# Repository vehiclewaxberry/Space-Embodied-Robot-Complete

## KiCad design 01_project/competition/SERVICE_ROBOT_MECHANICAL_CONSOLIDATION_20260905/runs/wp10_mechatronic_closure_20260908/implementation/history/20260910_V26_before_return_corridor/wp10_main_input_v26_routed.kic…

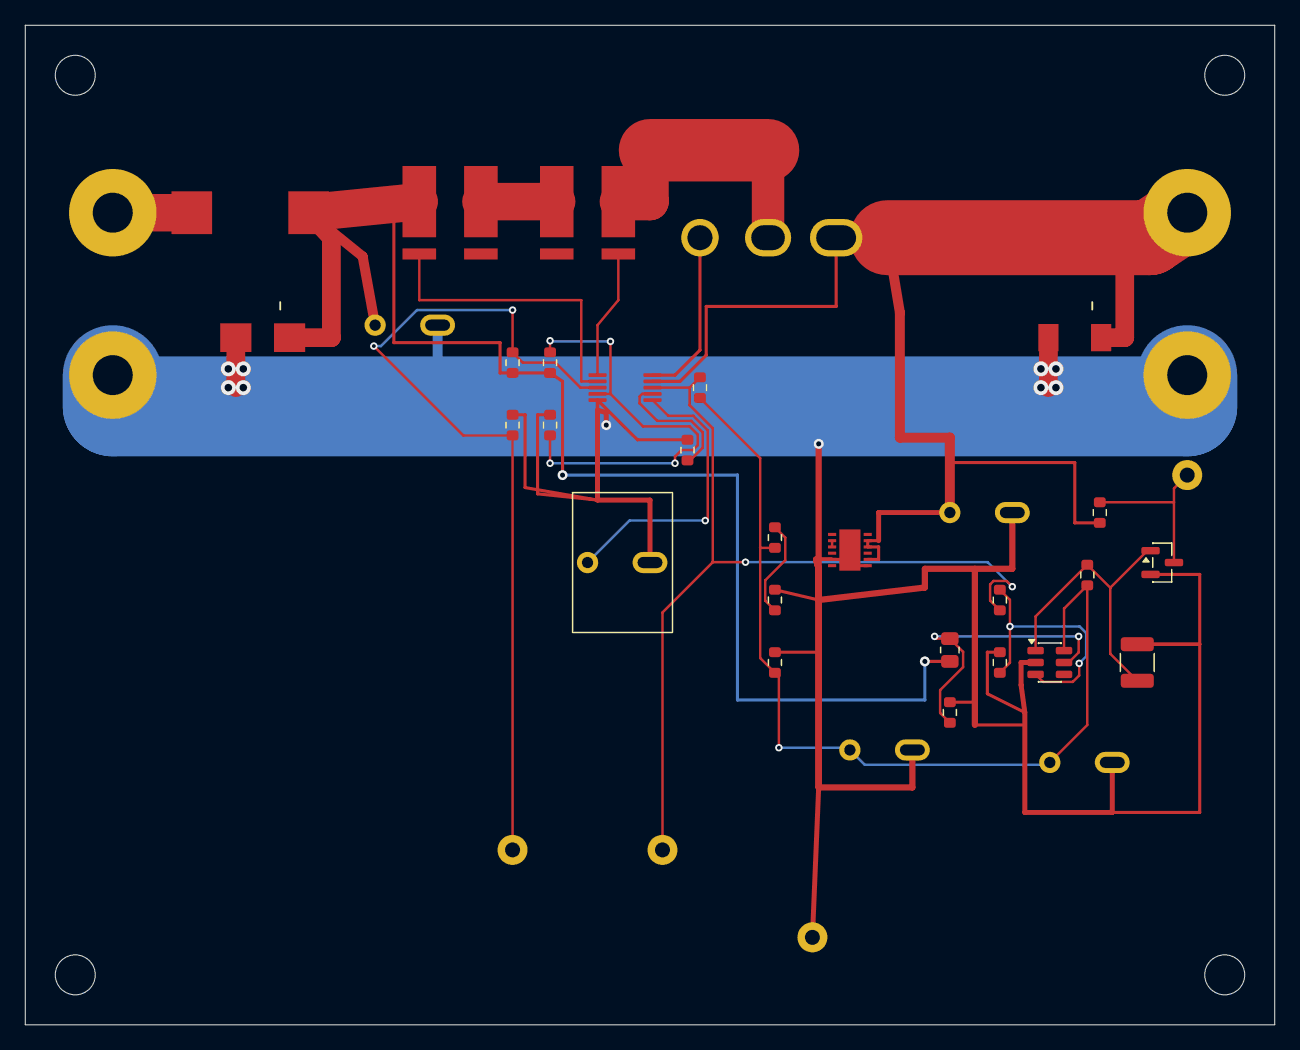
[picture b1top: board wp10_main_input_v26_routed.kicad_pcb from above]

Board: 2 copper layers, 100.0 x 80.0 mm, 43 parts (0 on the bottom side), 18 nets.

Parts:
C201: MKP2C041001N00JSSD; C201_MKP2_1uF_P5_Slot2
C202, C213: MKP2D031001F00JSSD; MKP2_D031001F00_P5_Slot2
C211: MKS2D041501M00JSSD; MKS2_D041501M00_P5_Slot2
C212: MKS2D044701O00JSSD; MKS2_D044701O00_P5_Slot2
D201: SMBJ30A-13-F; SMBJ30A_A1K2
D202: STPS3H100U; STPS3H100U_A1K2
F201: 1025HC30-RTR; Fuse_Eaton_1025HC_20to30A_3p25x3p43_P9p35
MH1, MH2, MH3, MH4: (no value)
PORT_BAT_PLUS: PROJECT_WIRE_LANDING_NOT_OEM_CONNECTOR
PORT_BAT_RETURN: PROJECT_WIRE_LANDING_NOT_OEM_CONNECTOR
PORT_CHB_PLUS: PROJECT_WIRE_LANDING_NOT_OEM_CONNECTOR
PORT_CHB_RETURN: PROJECT_WIRE_LANDING_NOT_OEM_CONNECTOR
PORT_ENABLE: PROJECT_WIRE_LANDING_NOT_OEM_CONNECTOR
PORT_PGD: PROJECT_WIRE_LANDING_NOT_OEM_CONNECTOR
PORT_RESET: PROJECT_WIRE_LANDING_NOT_OEM_CONNECTOR
PORT_SIGNAL_RETURN: PROJECT_WIRE_LANDING_NOT_OEM_CONNECTOR
Q201: IXTH75N10L2; IXTH_TO247_G1D2S3_P5p45_Slots
Q204: 2N7002K-7; SOT-23
R201: WSLP27262L000FEA; WSLP2726_KelvinSplit_TwoTerminals
R202: WSLP2726L2000FEA; WSLP2726_KelvinSplit_TwoTerminals
R203: TNPW060347K5BEEA; R_0603_1608Metric
R204: TNPW06035K90BEEA; R_0603_1608Metric
R205: TNPW0603120KBEEA; R_0603_1608Metric
R206, R212, R216: TNPW060310K0BEEA; R_0603_1608Metric
R207: TNPW060330K1BEEA; R_0603_1608Metric
R211: TNPW060338K3BEEA; R_0603_1608Metric
R213: TNPW06034K70FEEA; R_0603_1608Metric
R214: TNPW06033K48BEEA; R_0603_1608Metric
R215: TNPW0805374KBEEA; R_0805_2012Metric
R217: TNPW060333K0FEEA; R_0603_1608Metric
R218: TNPW12102M20FEEA; R_1210_3225Metric
R219: TNPW0603100KFEEA; R_0603_1608Metric
R220: TNPW060310K0FEEA; R_0603_1608Metric
R221: TNPW0603100RFEEA; R_0603_1608Metric
U201: LM5069MM-1; LM5069_DGS10_P0p5_NoEP
U205: LT3013EDE#PBF; LT3013_DE12_EP13_3x4_Pin1LeftTop
U206: TPS3808G01DBVR; SOT-23-6

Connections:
WP10_BAT_PROTECTED_PLUS: F201.1, PORT_BAT_PLUS.1
WP10_CHB_ENABLE: PORT_ENABLE.1, Q204.3, R219.2
WP10_CHB_ENABLE_GATE: Q204.1, R217.2, R218.1, U206.1
WP10_HS_OVLO: R205.2, R206.1, U201.4
WP10_HS_PGD: PORT_PGD.1, R214.2, R221.1, U201.8
WP10_HS_POWER_LIMIT: R207.1, U201.7
WP10_HS_TIMER: C201.1, U201.6
WP10_HS_UVLO: PORT_RESET.1, R203.2, R204.1, U201.3
WP10_INPUT_RETURN: C201.2, C202.2, C211.2, C212.2, C213.2, D201.1, D202.1, PORT_BAT_RETURN.1, PORT_CHB_RETURN.1, PORT_SIGNAL_RETURN.1, Q204.2, R204.2, R206.2, R207.2, R212.2, R213.2, R216.2, R218.2, R220.2, U201.5, U205.5, U205.7, U205.13, U206.2
WP10_MAIN_FUSED: C202.1, D201.2, F201.2, R201.1, R203.1, R205.1, R215.1, U201.2
WP10_MAIN_GATE: Q201.1, U201.10
WP10_MAIN_SENSE: Q201.2, R202.2, U201.1
WP10_PRECHARGED_PLUS: C211.1, D202.2, PORT_CHB_PLUS.1, Q201.3, R219.1, U201.9, U205.8, U205.10, U205.11
WP10_SENSE_MID: R201.2, R202.1
WP10_STARTUP_ADJ: R211.2, R212.1, U205.4
WP10_STARTUP_BIAS: C212.1, C213.1, R211.1, R213.1, R214.1, R217.1, U205.2, U205.3, U206.6
WP10_STARTUP_INPUT_SENSE: R215.2, R216.1, U206.5
WP10_STARTUP_PG_RECEIVER: R220.1, R221.2, U206.3

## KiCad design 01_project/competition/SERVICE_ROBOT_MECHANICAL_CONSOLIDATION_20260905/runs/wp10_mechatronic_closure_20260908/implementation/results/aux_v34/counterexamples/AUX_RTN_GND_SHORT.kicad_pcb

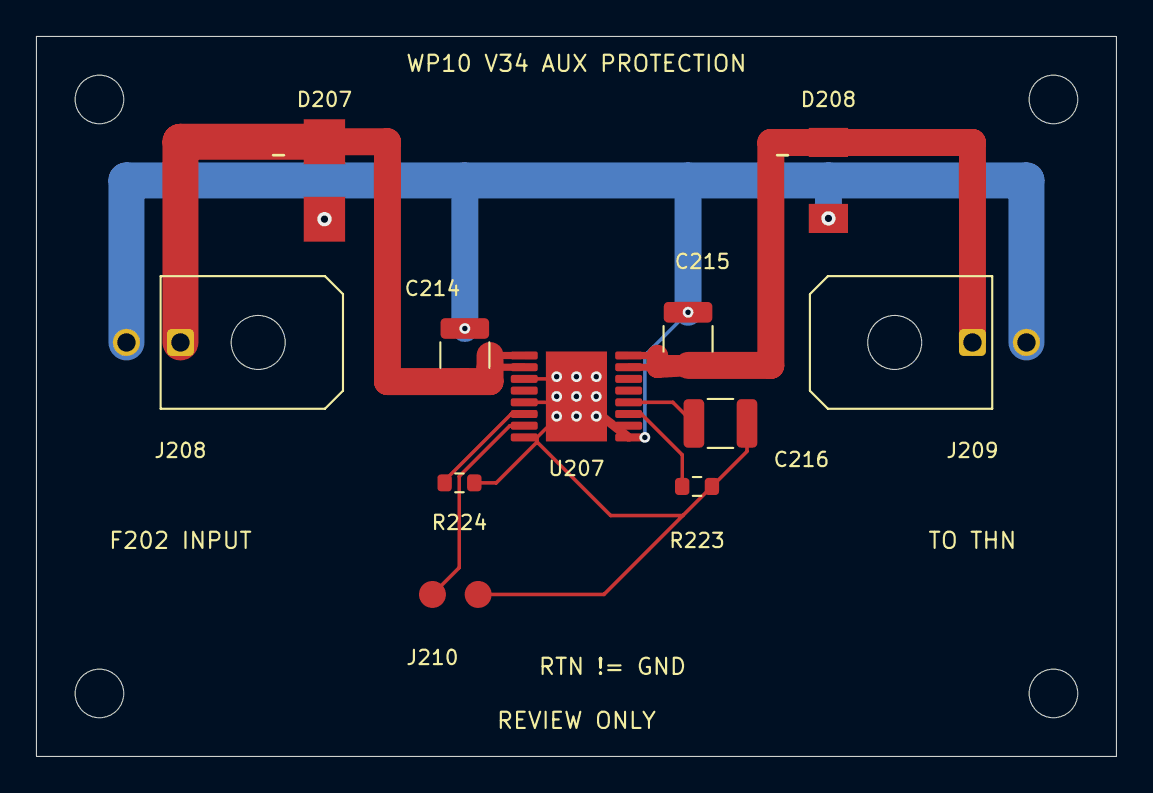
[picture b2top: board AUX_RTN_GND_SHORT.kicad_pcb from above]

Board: 2 copper layers, 60.0 x 40.0 mm, 15 parts (0 on the bottom side), 8 nets.

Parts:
C214, C215, C216: 100nF 100V C0G; C_1210_3225Metric
D207: SMBJ30CA-13-F; SMBJ30A_A1K2
D208: STPS3H100U; STPS3H100U_K1A2
J208: 43045-0200 IN; Molex_Micro-Fit_3.0_43045-0200_2x01_P3.00mm_Horizontal
J209: 43045-0200 TO_THN; Molex_Micro-Fit_3.0_43045-0200_2x01_P3.00mm_Horizontal
J210: LOCAL_RESET_TEST_PADS; ResetTestPads
MH34_1, MH34_2, MH34_3, MH34_4: M2.5 NPTH 2.7mm; MountingHole_2.7mm_M2.5
R223: 5.36k; R_0603_1608Metric
R224: 402k; R_0603_1608Metric
U207: TPS26600PWPR; TPS26600_PWP16_EP17

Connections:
WP10_AUX_DVDT: C216.1, U207.12
WP10_AUX_FUSED: C214.1, D207.2, J208.1, U207.1, U207.2
WP10_AUX_ILIM: R223.1, U207.11
WP10_AUX_LIMITED: C215.1, D208.1, J209.1, U207.15, U207.16
WP10_AUX_MODE: R224.1, U207.6
WP10_AUX_PROTECT_RTN: C216.2, J210.2, R223.2, R224.2, U207.3, U207.5, U207.8, U207.17
WP10_AUX_RESET: J210.1, U207.7
WP10_INPUT_RETURN: C214.2, C215.2, D207.1, D208.2, J208.2, J209.2, U207.9

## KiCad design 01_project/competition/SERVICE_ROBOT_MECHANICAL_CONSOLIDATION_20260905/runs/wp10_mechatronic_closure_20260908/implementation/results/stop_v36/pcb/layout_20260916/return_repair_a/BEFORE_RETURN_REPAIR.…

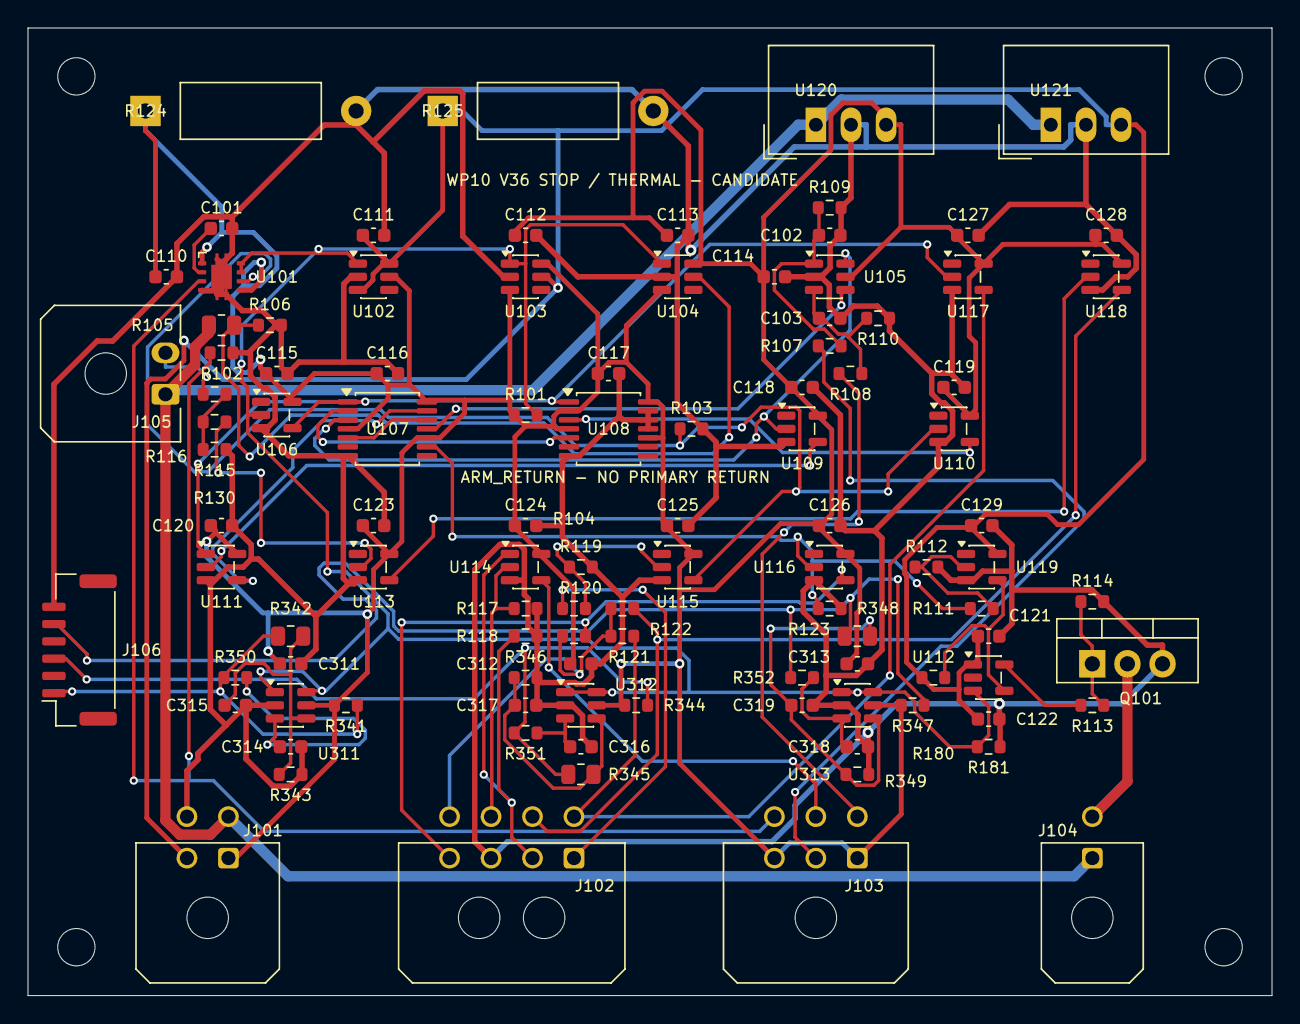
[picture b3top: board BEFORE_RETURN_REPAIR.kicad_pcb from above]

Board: 2 copper layers, 90.0 x 70.0 mm, 107 parts (0 on the bottom side), 49 nets.

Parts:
C101: C0603C121F5GACTU / C0603C121F5GACTU; C_0603_1608Metric
C102, C103, C122: C0603C105K4RACTU / 1uF X7R 16V 10%; C_0603_1608Metric
C110, C111, C112, C113, C114, C115, C116, C117, C118, C119, C120, C121, C123, C124, C125, C126, C127, C128, C129, C311, C312, C313: C0603C104K3RACTU / 100nF X7R 25V 10%; C_0603_1608Metric
C314, C315, C316, C317, C318, C319: 1nF; C_0603_1608Metric
HSTOP1, HSTOP2, HSTOP3, HSTOP4: M2.5; MountingHole_2.7mm_M2.5
J101: 430450400; Molex_Micro-Fit_3.0_43045-0400_2x02_P3.00mm_Horizontal
J102: 430450800; Molex_Micro-Fit_3.0_43045-0800_2x04_P3.00mm_Horizontal
J103: 430450600; Molex_Micro-Fit_3.0_43045-0600_2x03_P3.00mm_Horizontal
J104: 430450200; Molex_Micro-Fit_3.0_43045-0200_2x01_P3.00mm_Horizontal
J105: 436500200; Molex_Micro-Fit_3.0_43650-0200_1x02_P3.00mm_Horizontal
J106: SM06B-GHS-TB; JST_GH_SM06B-GHS-TB_1x06-1MP_P1.25mm_Horizontal
Q101: IRL630PbF / IRL630PbF; TO-220-3_Vertical
R101: 4.7k; R_0603_1608Metric
R102, R107, R108, R112, R114, R117, R118, R120, R121, R122: CRCW060310K0FKEA / 10k 1%; R_0603_1608Metric
R103, R119, R123: CRCW060347K0FKEA / 47k 1%; R_0603_1608Metric
R104, R116: CRCW06031K00FKEA / 1k 1%; R_0603_1608Metric
R105: TNPW0805510KBEEA / 510k 0.1% 25ppm; R_0805_2012Metric
R106: TNPW060310K0BEEA / 10k 0.1% 25ppm; R_0603_1608Metric
R109, R110: CRCW0603100KFKEA / 100k 1%; R_0603_1608Metric
R111: 100; R_0603_1608Metric
R113: CRCW060322R0FKEA / 22R 1%; R_0603_1608Metric
R115: CRCW060322K0FKEA / 22k 1% 100ppm/C; R_0603_1608Metric
R124: PR02000202409JA100 / 24R 5% 250ppm/C 2W; Vishay_PR02_P15_24
R125: PR02000203909JA100 / 39R 5% 250ppm/C 2W; Vishay_PR02_P15_24
R130: CRCW06033K90FKEA / 3.9k 1% 100ppm/C; R_0603_1608Metric
R180: 10k; R_0603_1608Metric
R181: 47k; R_0603_1608Metric
R341, R344, R347: 8.2k_0.1pct_25ppm; R_0603_1608Metric
R342, R345, R348: 649k_0.1pct_25ppm; R_0805_2012Metric
R343, R346, R349: 100k_0.1pct_25ppm; R_0603_1608Metric
R350, R351, R352: 1k; R_0603_1608Metric
U101: TPS3431SDRBR / TPS3431SDRBR; TPS3431_DRB0008A
U102: TPS3808G33DBVR / TPS3808G33DBVR; SOT-23-6
U103: TPS3808G50DBVR / TPS3808G50DBVR; SOT-23-6
U104: TPS3808G01DBVR / TPS3808G01DBVR; SOT-23-6
U105: SN74LVC2G17DBVR / SN74LVC2G17DBVR; SOT-23-6
U106, U113, U115: SN74LVC1G17DBVR / SN74LVC1G17DBVR; SOT-23-5
U107, U108: SN74LVC74APWR / SN74LVC74APWR; TSSOP-14_4.4x5mm_P0.65mm
U109, U110: SN74LVC1G04DBVR / SN74LVC1G04DBVR; SOT-23-5
U111, U114: SN74LVC1G08DBVR / SN74LVC1G08DBVR; SOT-23-5
U112: UCC27517DBVR; SOT-23-5
U116, U117, U118: SN74LVC1G07DBVR / SN74LVC1G07DBVR; SOT-23-5
U119: SN74LV1T04DBVR; SOT-23-5
U120: TSR 1-2433 / TSR 1-2433; Converter_DCDC_TRACO_TSR-1_THT
U121: TSR 1-2450 / TSR 1-2450; Converter_DCDC_TRACO_TSR-1_THT
U311, U312, U313: TLV6700DDCR; SOT-23-6

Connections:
/Actual watchdog and contactor driver/ARMED: U107.5, U107.12
/Actual watchdog and contactor driver/AUX_CLOSED_3V3: U113.4, U118.2
/Actual watchdog and contactor driver/AUX_DIV: R115.2, R116.1, R130.1
/Actual watchdog and contactor driver/AUX_SENSE: R116.2, U113.2
/Actual watchdog and contactor driver/AUX_STATUS_MCU: J102.6, R122.2, U118.4
/Actual watchdog and contactor driver/BUS_MONITOR_OK: J102.7, R117.1, U114.2
/Actual watchdog and contactor driver/CWD: C101.1, U101.2
/Actual watchdog and contactor driver/EN_STOP: J103.6, R102.1, U101.3
/Actual watchdog and contactor driver/GATE_DRV: R113.1, U112.5
/Actual watchdog and contactor driver/HB_SEEN: U107.2, U108.5
/Actual watchdog and contactor driver/HEARTBEAT_FILTER: R104.2, R119.1, U115.2
/Actual watchdog and contactor driver/HEARTBEAT_IN: J102.1, R104.1
/Actual watchdog and contactor driver/HW_PERMIT_IN: J102.2, R118.1, U114.1
/Actual watchdog and contactor driver/K1_GATE: Q101.1, R113.2, R114.1
/Actual watchdog and contactor driver/MCU_VIO: J102.8, R120.1, R121.1, R122.1
/Actual watchdog and contactor driver/PERMIT_BEFORE_STOP: J103.5, U114.4
/Actual watchdog and contactor driver/RESET_CONTACT: J103.2, R107.1
/Actual watchdog and contactor driver/RESET_EDGE: U105.6, U107.3, U109.2
/Actual watchdog and contactor driver/RESET_N: U109.4, U111.2
/Actual watchdog and contactor driver/RESET_RC: C102.1, R107.2, R109.1, U105.1
/Actual watchdog and contactor driver/RUN_CLEAR_N: U107.13, U111.4
/Actual watchdog and contactor driver/RUN_DRIVE: R111.2, R112.1, U119.2
/Actual watchdog and contactor driver/RUN_INHIBIT_5V: R180.2, U112.4, U119.4
/Actual watchdog and contactor driver/RUN_LATCH: R111.1, R123.1, U107.9, U116.2
/Actual watchdog and contactor driver/RUN_STATUS_MCU: J102.4, R120.2, U116.4
/Actual watchdog and contactor driver/SAFE_N: U106.4, U107.1, U108.1, U111.1, U117.2
/Actual watchdog and contactor driver/SAFE_STATUS_MCU: J102.5, R121.2, U117.4
/Actual watchdog and contactor driver/SENSE_24V: R105.2, R106.1, U104.5
/Actual watchdog and contactor driver/START_CONTACT: J103.4, R108.1
/Actual watchdog and contactor driver/START_EDGE: U105.4, U107.11
/Actual watchdog and contactor driver/START_RC: C103.1, R108.2, R110.1, U105.3
/Actual watchdog and contactor driver/STOP_5V: C111.1, C121.1, C122.1, C129.1, J101.2, R125.1, R180.1, U102.3, U102.6, U103.5, U112.1, U119.5, U121.3
/Actual watchdog and contactor driver/WDI: R103.1, U101.6, U110.2, U115.4
/Actual watchdog and contactor driver/WDI_FALL: U108.3, U110.4
WP10_ARM_RETURN: C101.2, C102.2, C103.2, C110.2, C111.2, C112.2, C113.2, C114.2, C115.2, C116.2, C117.2, C118.2, C119.2, C120.2, C121.2, C122.2, C123.2, C124.2, C125.2, C126.2, C127.2, C128.2, C129.2, C311.2, C312.2, C313.2, C314.2, C315.2, C316.2, C317.2, C318.2, C319.2, J101.4, J102.3, J106.2, J106.4, J106.6, Q101.3, R102.2, R103.2, R106.2, R109.2, R110.2, R112.2, R114.2, R117.2, R118.2, R119.2, R123.2, R124.2, R125.2, R130.2, R181.2, R343.2, R346.2, R349.2, U101.4, U101.9, U102.2, U103.2, U104.2, U105.2, U106.3, U107.7, U108.7, U108.11, U108.12, U108.13, U109.3, U110.3, U111.3, U112.2, U113.3, U114.3, U115.3, U116.3, U117.3, U118.3, U119.3, U120.2, U121.2, U311.2, U312.2, U313.2
WP10_BRAKE_STOP_3V3: C110.1, C112.1, C113.1, C114.1, C115.1, C116.1, C117.1, C118.1, C119.1, C120.1, C123.1, C124.1, C125.1, C126.1, C127.1, C128.1, C311.1, C312.1, C313.1, J101.1, J103.1, J103.3, R101.1, R124.1, R341.1, R344.1, R347.1, U101.1, U101.5, U102.5, U103.3, U103.6, U104.3, U104.6, U105.5, U106.5, U107.4, U107.10, U107.14, U108.2, U108.4, U108.10, U108.14, U109.5, U110.5, U111.5, U113.5, U114.5, U115.5, U116.5, U117.5, U118.5, U120.3, U311.5, U312.5, U313.5
WP10_BRAKE_TEMP_1: J106.1, R341.2, R342.1, R350.1
WP10_BRAKE_TEMP_2: J106.3, R344.2, R345.1, R351.1
WP10_BRAKE_TEMP_3: J106.5, R347.2, R348.1, R352.1
WP10_BRAKE_TEMP_IN_1: C314.1, R350.2, U311.3
WP10_BRAKE_TEMP_IN_2: C316.1, R351.2, U312.3
WP10_BRAKE_TEMP_IN_3: C318.1, R352.2, U313.3
WP10_BRAKE_TEMP_OPEN_1: C315.1, R342.2, R343.1, U311.4
WP10_BRAKE_TEMP_OPEN_2: C317.1, R345.2, R346.1, U312.4
WP10_BRAKE_TEMP_OPEN_3: C319.1, R348.2, R349.1, U313.4
WP10_BRAKE_THERMAL_FAULT_N: R101.2, R181.1, U101.7, U101.8, U102.1, U103.1, U104.1, U106.2, U112.3, U311.1, U311.6, U312.1, U312.6, U313.1, U313.6
WP10_LEGACY_079: J105.2, R115.1
WP10_LEGACY_080: J104.2, Q101.2
WP10_STOP_24V: J101.3, J104.1, J105.1, R105.1, U120.1, U121.1
